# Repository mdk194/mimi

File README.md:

# mimi keyboard

54 keys split keyboard.
reversible pcb and 3d printed cases

# ZMK
- main branch: left side as master
- dongle branch: include config for dongle

# TODO
- qmk firmware
- test trrs socket

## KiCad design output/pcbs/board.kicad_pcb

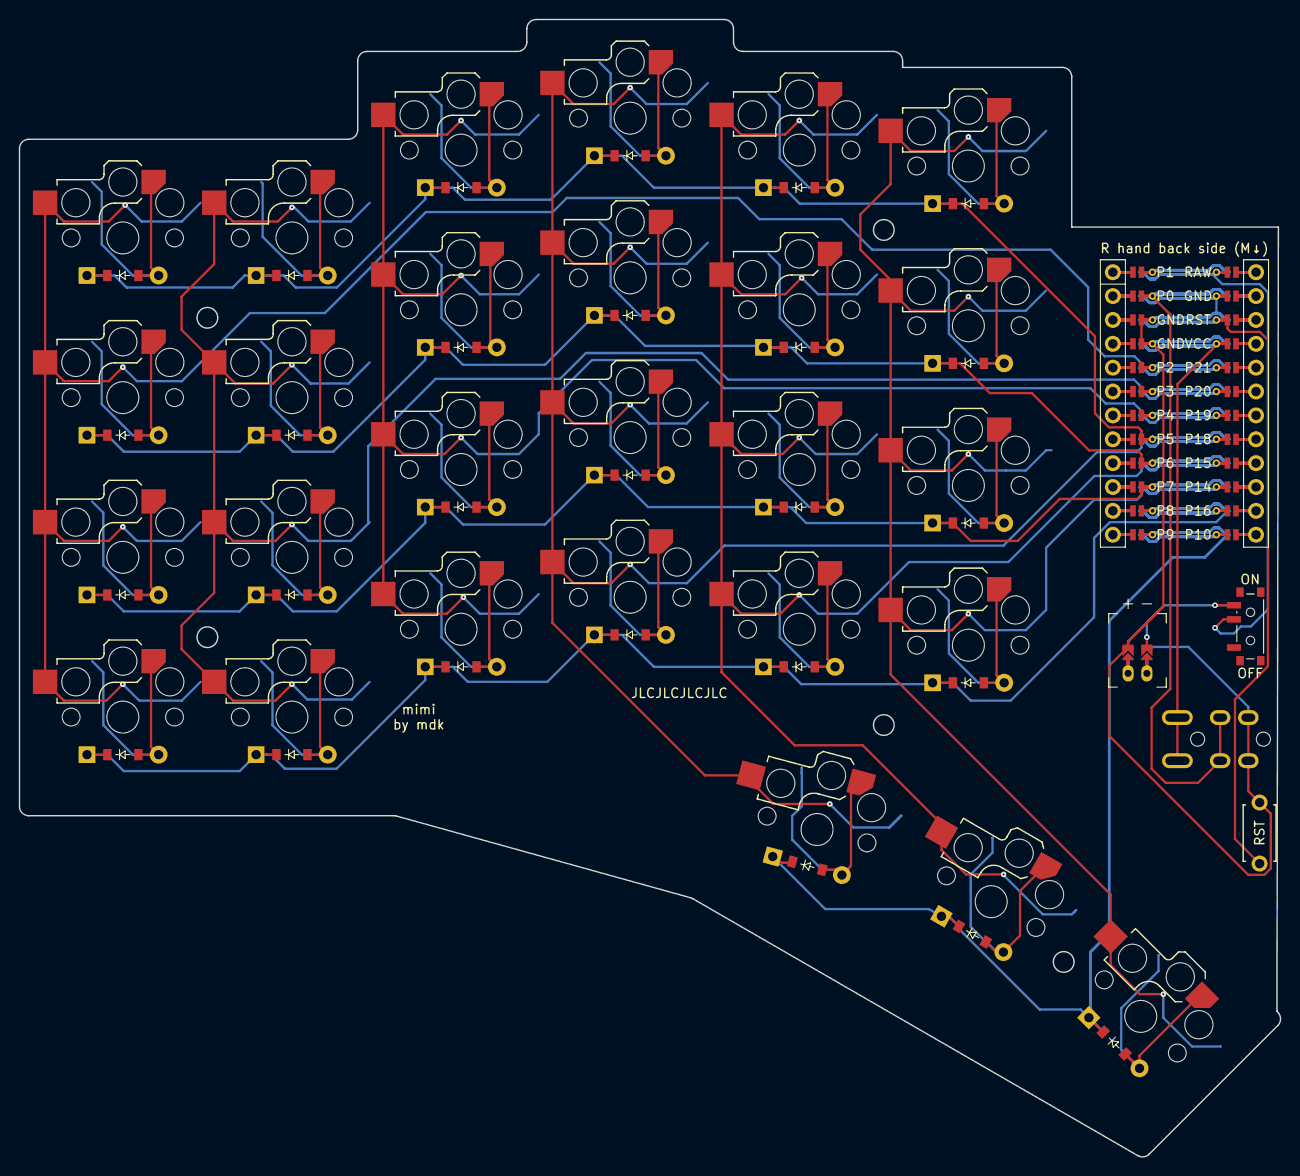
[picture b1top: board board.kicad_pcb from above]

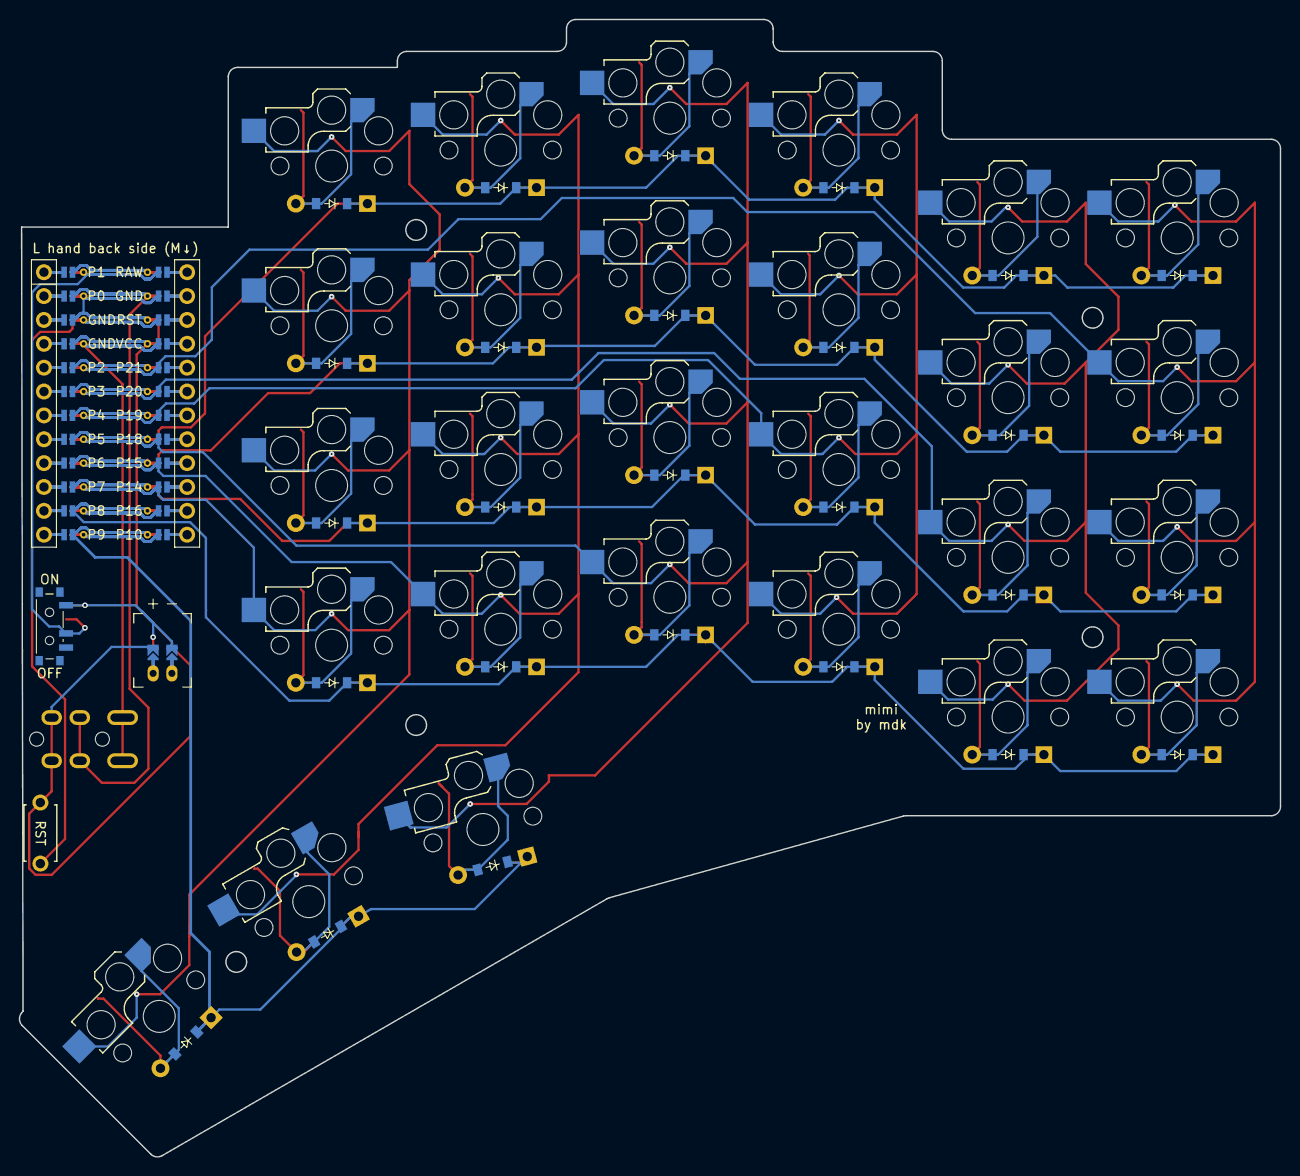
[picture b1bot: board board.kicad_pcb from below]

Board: 2 copper layers, 134.2 x 121.1 mm, 59 parts (27 on the bottom side), 46 nets.

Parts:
D1, D2, D3, D4, D5, D6, D7, D8, D9, D10, D11, D12, D13, D14, D15, D16, D17, D18, D19, D20, D21, D22, D23, D24, D25, D26, D27: diode_tht_sod123
JST1: battery_connector_jst_ph_2
MCU1: mcu_nice_nano
PWR1: power_switch_smd_side
RST1: reset_switch_tht_top
S1, S2, S3, S4, S5, S6, S7, S8, S9, S10, S11, S12, S13, S14, S15, S16, S17, S18, S19, S20, S21, S22, S23, S24, S25, S26, S27: switch_choc_v1_v2
TRRS1: trrs_pj320a (reversible, symmetric)

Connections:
BAT_P: JST1.1, PWR1.1, PWR1.3
GND: JST1.2, MCU1.102, MCU1.121, MCU1.122, RST1.2, TRRS1.2
JST1_1: JST1.11, JST1.21, JST1.31
JST1_2: JST1.12, JST1.22, JST1.32
P0: MCU1.123, TRRS1.3
P5: D4.1, D8.1, D12.1, D16.1, D20.1, D24.1, MCU1.117
P6: D3.1, D7.1, D11.1, D15.1, D19.1, D23.1, MCU1.116
P7: D2.1, D6.1, D10.1, D14.1, D18.1, D22.1, MCU1.115
P8: D1.1, D5.1, D9.1, D13.1, D17.1, D21.1, MCU1.114
P9: D25.1, D26.1, D27.1, MCU1.113
P14: MCU1.110, S21.2, S22.2, S23.2, S24.2, S27.2
P15: MCU1.109, S17.2, S18.2, S19.2, S20.2, S26.2
P18: MCU1.108, S13.2, S14.2, S15.2, S16.2, S25.2
P19: MCU1.107, S9.2, S10.2, S11.2, S12.2
P20: MCU1.106, S5.2, S6.2, S7.2, S8.2
P21: MCU1.105, S1.2, S2.2, S3.2, S4.2
RAW: MCU1.101, PWR1.2
RST: MCU1.103, RST1.1
VCC: MCU1.104, TRRS1.4
far_thumb: D27.2, S27.1
home_thumb: D26.2, S26.1
index_bottom: D17.2, S17.1
index_home: D18.2, S18.1
index_number: D20.2, S20.1
index_top: D19.2, S19.1
inner_bottom: D21.2, S21.1
inner_home: D22.2, S22.1
inner_number: D24.2, S24.1
inner_top: D23.2, S23.1
middle_bottom: D13.2, S13.1
middle_home: D14.2, S14.1
middle_number: D16.2, S16.1
middle_top: D15.2, S15.1
near_thumb: D25.2, S25.1
outer_bottom: D1.2, S1.1
outer_home: D2.2, S2.1
outer_number: D4.2, S4.1
outer_top: D3.2, S3.1
pinky_bottom: D5.2, S5.1
pinky_home: D6.2, S6.1
pinky_number: D8.2, S8.1
pinky_top: D7.2, S7.1
ring_bottom: D9.2, S9.1
ring_home: D10.2, S10.1
ring_number: D12.2, S12.1
ring_top: D11.2, S11.1

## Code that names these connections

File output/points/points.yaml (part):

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        autobind: 10
        skip: false
        asym: both
        colrow: pinky_bottom
        name: matrix_pinky_bottom
        footprints:
            choc_hotswap:
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        autobind: 10
        skip: false
        asym: both
        colrow: pinky_home
        name: matrix_pinky_home
        footprints:
            choc_hotswap:
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        autobind: 10
        skip: false
        asym: both
        colrow: pinky_top
        name: matrix_pinky_top
        footprints:
            choc_hotswap:
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        autobind: 10
        skip: false
        asym: both
        colrow: pinky_number
        name: matrix_pinky_number
        footprints:
            choc_hotswap:
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
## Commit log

2025-03-13 init
2025-03-13 routed board
2025-03-13 add gerbers files
2025-03-13 fix readme images
2025-03-17 fix trrs pin
2025-03-17 fix trrs routing
2025-03-17 re-plot gerbers and images
2025-03-17 init zmk
2025-03-17 zmk: init config
2025-03-17 zmk: add zephyr
2025-04-03 cases: fix mcu usb port size
2025-04-03 trrs: enable back symmetric + serial pin
2025-04-06 add wireless top case, add reset button hole
2025-04-20 zmk: add home row mode config
2025-04-20 zmk: change mt flavor to balanced
2025-04-21 swap minus and equal
2025-04-21 zmk: copy default keymap layer to config
2025-04-25 zmk: report battery for both side
2025-05-01 readme: add note about dongle branch
2025-05-01 zmk: dongle config
2025-05-01 zmk: use homemode
2025-05-03 zmk: enable deep sleep
2025-05-31 keymap: use combo for brackets
2025-05-31 zmk: unify tapping term, quick tap, prior idle ms
2025-06-04 zmk: reduce combo to 20ms
2025-06-08 zmk: raise debounce time to 10ms
2025-06-18 keymap: disable brackets combo
2025-06-18 keymap: shift and alt mode tap hold-prefered
2025-06-19 keymap: reduce combo timeout 15ms
2025-10-02 keymap: combo: require-prior-idle-ms = <160>
2025-10-04 keymap: disable left, right combo
2026-05-25 fix: update board to nice_nano@2.0.0
2026-05-25 fix: build.yaml, remove deprecated CONFIG_ZMK_BLE_EXPERIMENTAL_CONN
2026-05-25 config/mimi.conf: add back CONFIG_ZMK_BLE_EXPERIMENTAL_CONN=y
2026-06-24 swap mouse move and arrow
